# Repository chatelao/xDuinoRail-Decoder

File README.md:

View this project on [CADLAB.io](https://cadlab.io/project/27556). 

# xDuinoRail-Decoder

The friendly decoder development plattform for model railroad tinkers.

## Target plattforms

### Arduino (UNO R3) formfactor

The primary tinker formfactor is the "Arduino UNO R3":

| CPU | MCU | Vendor | Product Name & Page |
|--- | --- | --- | --- | 
| ? Atmega ? | Atmega328 | Arduino & Clones|
|--- | Atmega32u4 | Arduino & Clones |
|--- | AtmegaMEGA | Arduino & Clones |
| ARM M0+ | SAMD21 | Adafruit | [Metro M0 Express](https://www.adafruit.com/product/3505) | 
| ARM M0+ | SAMD21 | SparkFun |
| ARM M4 | SAMD51 | Adafruit | [Metro M4 Express](https://www.adafruit.com/product/4000) | 
| Dual ARM M0+ | RP2040 | Adafruit | [Metro RP2040](https://www.adafruit.com/product/5786) | 
| ARM M4 | nRF52840 | Nordic | [nRF52840 DK](https://www.mouser.ch/ProductDetail/Nordic-Semiconductor/nRF52840-DK?qs=F5EMLAvA7IA76ZLjlwrwMw%3D%3D&gad_source=1&gclid=CjwKCAiA1fqrBhA1EiwAMU5m_9iVmasRrajTl6bT0wZal1_tMu6lTCWF3Ct0FWfQw9FYF_E3vaRdBRoC_tcQAvD_BwE)
| ARM M4 | nRF52840 | Waveshare | [nRF52840 Bluetooth 5.0 Evaluation Kit](https://www.waveshare.com/nrf52840-eval-kit.htm)
| RV32IMAC | SiFive RISC-V | SparkFun | [SparkFun RED-V RedBoard](https://www.sparkfun.com/products/15594) 
| RV32IMAFC | WCH RISC-V | AliExpress | [CH32V307V-EVT-R1 CH32V307 Evaluation Board RISC-V](https://de.aliexpress.com/item/1005004151524708.html)

### Decoder development for XIAO formfactor

The [XIAO](http://www.ulisp.com/show?3NRF) formfactor may even fit some H0 locomotives, so COMING SOON:

| CPU | MCU | Vendor | Product Name & Page |
|--- | --- | --- | --- | 
| ARM M0+ | SAMD21 | SeeedStudio | [XIAO SAMD21](https://wiki.seeedstudio.com/Seeeduino-XIAO)
| Dual ARM M0+ | RP2040 | SeeedStudio | [XIAO RP2040](https://wiki.seeedstudio.com/XIAO-RP2040/)
| ARM M4 | nRF52840  | SeeedStudio | [XIAO BLE](https://wiki.seeedstudio.com/XIAO_BLE/)
| Xtensa LX7  | ESP32-S3 | SeeedStudio | [ESP32-S3](https://wiki.seeedstudio.com/xiao_esp32s3_getting_started/)
| RV32IMC  | ESP32-C3 | SeeedStudio | [ESP32-C3](https://wiki.seeedstudio.com/XIAO_ESP32C3_Getting_Started/) 
| ARM M0+ | SAMD21 | Adafruit | [QT Py SAMD21](https://www.adafruit.com/product/4600) 
| Dual ARM M0+ | RP2040 | Adafruit | [QT Py RP2040](https://www.adafruit.com/product/4900) 
| RV32IMC | ESP32-C3 | Adafruit | [QT Py ESP32-C3](https://www.adafruit.com/product/5405)
| Xtensa LX7 |  ESP32-S2 |Adafruit | [QT Py ESP32-S2](https://www.adafruit.com/product/5325)
| Xtensa LX7  | ESP32-S3 | Adafruit | [QT Py ESP32-S3](https://www.adafruit.com/product/5426)

## Features
Power:
- It extracts power from the rails.

Data
- It extracts DCC raw signals  from the rails.
- It provides raw (RailCom) feedback to the rails.

The data pins are X (input) and Y (output) per default (no soldering needed, but can be reassigned to any other GPIO-Pins.

## Excluded by purpose
- It doesn't include any power IO
- It doesn't include any MCU

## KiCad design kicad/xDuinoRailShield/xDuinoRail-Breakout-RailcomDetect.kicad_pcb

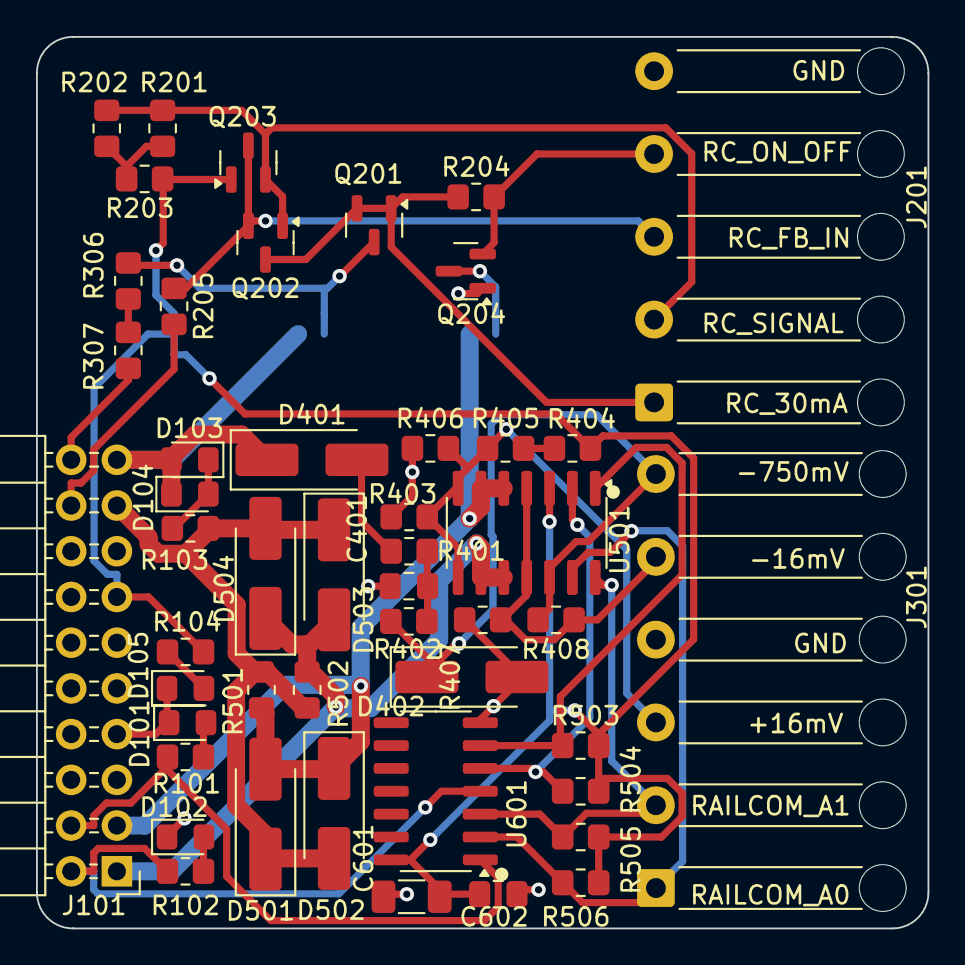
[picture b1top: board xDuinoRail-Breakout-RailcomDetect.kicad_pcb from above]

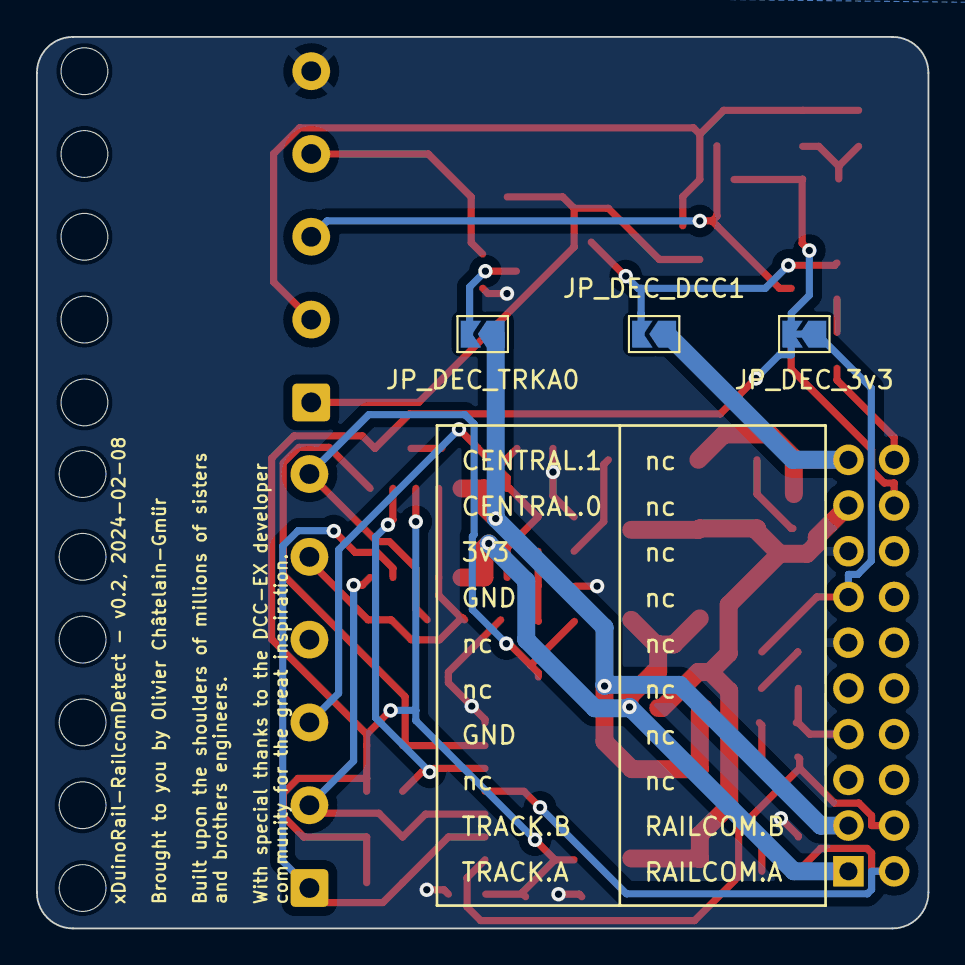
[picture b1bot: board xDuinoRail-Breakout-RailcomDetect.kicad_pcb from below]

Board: 2 copper layers, 49.5 x 49.5 mm, 51 parts (3 on the bottom side), 32 nets.

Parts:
C401: 47uF; C_0805_2012Metric_Pad1.18x1.45mm_HandSolder
C601: 100uF; C_1206_3216Metric_Pad1.33x1.80mm_HandSolder
C602: 100nF; C_0805_2012Metric_Pad1.18x1.45mm_HandSolder
D101: LED_BLUE; LED_0805_2012Metric_Pad1.15x1.40mm_HandSolder
D102: LED_GREEN; LED_0805_2012Metric_Pad1.15x1.40mm_HandSolder
D103: LED_YELLOW; LED_0805_2012Metric_Pad1.15x1.40mm_HandSolder
D104: LED_WHITE; LED_0805_2012Metric_Pad1.15x1.40mm_HandSolder
D105: LED_RED; LED_0805_2012Metric_Pad1.15x1.40mm_HandSolder
D401, D402: SM4007; D_SMA_Handsoldering
D501, D502, D503, D504: SS54; D_SMA_Handsoldering
J101: Conn_02x10_Odd_Even; PinHeader_2x10_P2.54mm_Horizontal
J201: Conn_01x05; SolderWire-0.5sqmm_1x05_P4.6mm_D0.9mm_OD2.1mm_Relief
J301: Conn_01x06; SolderWire-0.5sqmm_1x06_P4.6mm_D0.9mm_OD2.1mm_Relief
JP_DEC_3v3: SolderJumper_2_Open; SolderJumper-2_P1.3mm_Open_TrianglePad1.0x1.5mm
JP_DEC_DCC1: SolderJumper_2_Open; SolderJumper-2_P1.3mm_Open_TrianglePad1.0x1.5mm
JP_DEC_TRKA0: SolderJumper_2_Open; SolderJumper-2_P1.3mm_Open_TrianglePad1.0x1.5mm
Q201, Q204: S8050; SOT-23
Q202, Q203: S8550; SOT-23
R101, R102, R103, R104, R204, R205, R306, R307, R404, R405, R408, R503, R504, R505, R506: 10k; R_0805_2012Metric_Pad1.20x1.40mm_HandSolder
R201, R202, R203: 10R; R_0805_2012Metric_Pad1.20x1.40mm_HandSolder
R401, R402, R403, R406, R407: 220R; R_0805_2012Metric_Pad1.20x1.40mm_HandSolder
R501, R502: 2R; R_0805_2012Metric_Pad1.20x1.40mm_HandSolder
U501: LM339; SOIC-14_3.9x8.7mm_P1.27mm
U601: 74HC02; SOIC-14_3.9x8.7mm_P1.27mm

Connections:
+3V3: C601.1, C602.1, J101.13, JP_DEC_3v3.1 (A), JP_DEC_3v3.2 (B), Q203.1 (E), R104.1, R203.2, R404.2, R503.2, R504.2, R505.2, R506.2, U501.3 (V+), U601.14 (VCC)
+18mV: J301.3, R403.2, R405.1, R406.2, U501.7 (+), U501.8 (-)
-18mV: J301.5, R407.1, R408.1, U501.4 (-), U501.11 (+)
-750mV: D402.1 (K), J301.6, R402.1, R408.2, U501.12 (V-)
/CN_A2: J301.1, R506.1, U501.13, U601.2
/CN_A3: J301.2, R505.1, U501.14, U601.3
/CN_A4: R504.1, U501.2, U601.5
/CN_A5: R503.1, U501.1, U601.6
/DCC0: D501.1 (K), D502.2 (A), D503.1 (K), D504.2 (A), J101.17, R103.1, R501.2, R502.2
/DCC1: D103.2 (A), D104.1 (K), D401.1 (K), J101.19, JP_DEC_DCC1.1 (A)
/DECODER_DIGITAL: J101.20, R307.2
/DECODER_RAILCOM: J101.18, R205.2
/RAILCOM0: J101.4, R101.1, U601.1
/RAILCOM1: J101.2, R102.1, U601.4
/RC_GENERATOR0: JP_DEC_TRKA0.2 (B), Q204.3 (C)
/RC_GENERATOR1: JP_DEC_DCC1.2 (B), Q201.3 (C), R306.1
/TRACK_A0: D501.2 (A), D502.1 (K), J101.3, JP_DEC_TRKA0.1 (A), R501.1, U501.5 (+), U501.6 (-)
/TRACK_B0: D503.2 (A), D504.1 (K), J101.1, R502.1, U501.9 (+), U501.10 (-)
/centrale-railcom-feedback/central_railcom-power-source/DCC_NEG: C401.2, R401.1, R402.2
/rails_signal_feedback_dcc-railcom-8x50/15R: R201.2, R202.2, R203.1
/rails_signal_feedback_dcc-railcom-8x50/RC_CURR: J201.2, Q202.1 (E), Q203.2 (B), R201.1, R202.1
/rails_signal_feedback_dcc-railcom-8x50/RC_FB_IN: J201.3, Q202.2 (B), Q203.3 (C), R205.1
/rails_signal_feedback_dcc-railcom-8x50/RC_ON_OFF: J201.4, Q204.2 (B), R204.2
/rails_signal_feedback_dcc-railcom-8x50/RC_SIGNAL: J201.1, Q201.1 (E), Q201.2 (B), Q202.3 (C), R204.1
GND: C401.1, C601.2, C602.2, D101.1 (K), D102.1 (K), D105.1 (K), D402.2 (A), J101.7, J101.11, J101.15, J201.5, J301.4, Q204.1 (E), R403.1, R406.1, R407.2, U601.7 (GND)
unnamed: D101.2 (A), R101.2
unnamed: D102.2 (A), R102.2
unnamed: D103.1 (K), D104.2 (A), R103.2
unnamed: D105.2 (A), R104.2
unnamed: D401.2 (A), R401.2
unnamed: R306.2, R307.1
unnamed: R404.1, R405.2

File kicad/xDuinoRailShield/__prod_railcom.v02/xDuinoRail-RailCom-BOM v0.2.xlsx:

Reference | Value | Footprint | Qty | LCSC
C401 | 47uF | Capacitor_SMD:C_0805_2012Metric_Pad1.18x1.45mm_HandSolder | 1.0 | C16780
C601 | 100uF | Capacitor_SMD:C_1206_3216Metric_Pad1.33x1.80mm_HandSolder | 1.0 | C15008
C602 | 100nF | Capacitor_SMD:C_0805_2012Metric_Pad1.18x1.45mm_HandSolder | 1.0 | C49678
D101,D102 | LED_GREEN | LED_SMD:LED_0805_2012Metric_Pad1.15x1.40mm_HandSolder | 2.0 | C2297
D103 | LED_YELLOW | LED_SMD:LED_0805_2012Metric_Pad1.15x1.40mm_HandSolder | 1.0 | C2296
D104 | LED_WHITE | LED_SMD:LED_0805_2012Metric_Pad1.15x1.40mm_HandSolder | 1.0 | C34499
D105 | LED_RED | LED_SMD:LED_0805_2012Metric_Pad1.15x1.40mm_HandSolder | 1.0 | C84256
D401,D402 | SM4007 | Diode_SMD:D_SMA_Handsoldering | 2.0 | C64898
D501,D502,D503,D504 | SS54 | Diode_SMD:D_SMA_Handsoldering | 4.0 | C22452
Q201,Q204 | S8050 | Package_TO_SOT_SMD:SOT-23 | 2.0 | C2150
Q202,Q203 | S8550 | Package_TO_SOT_SMD:SOT-23 | 2.0 | C8542
R101,R102,R103,R104,R204,R205,R306,R307,R404,R405,R408,R503,R504,R505,R506 | 10k | Resistor_SMD:R_0805_2012Metric_Pad1.20x1.40mm_HandSolder | 15.0 | C17414
R201,R202,R203 | 10R | Resistor_SMD:R_0805_2012Metric_Pad1.20x1.40mm_HandSolder | 3.0 | C17415
R401,R402,R403,R406,R407 | 220R | Resistor_SMD:R_0805_2012Metric_Pad1.20x1.40mm_HandSolder | 5.0 | C17557
R501,R502 | 2R | Resistor_SMD:R_0805_2012Metric_Pad1.20x1.40mm_HandSolder | 2.0 | C22977
U501 | LM339 | Package_SO:SOIC-14_3.9x8.7mm_P1.27mm | 1.0 | C7948
U601 | 74HC02 | Package_SO:SOIC-14_3.9x8.7mm_P1.27mm | 1.0 | C5588

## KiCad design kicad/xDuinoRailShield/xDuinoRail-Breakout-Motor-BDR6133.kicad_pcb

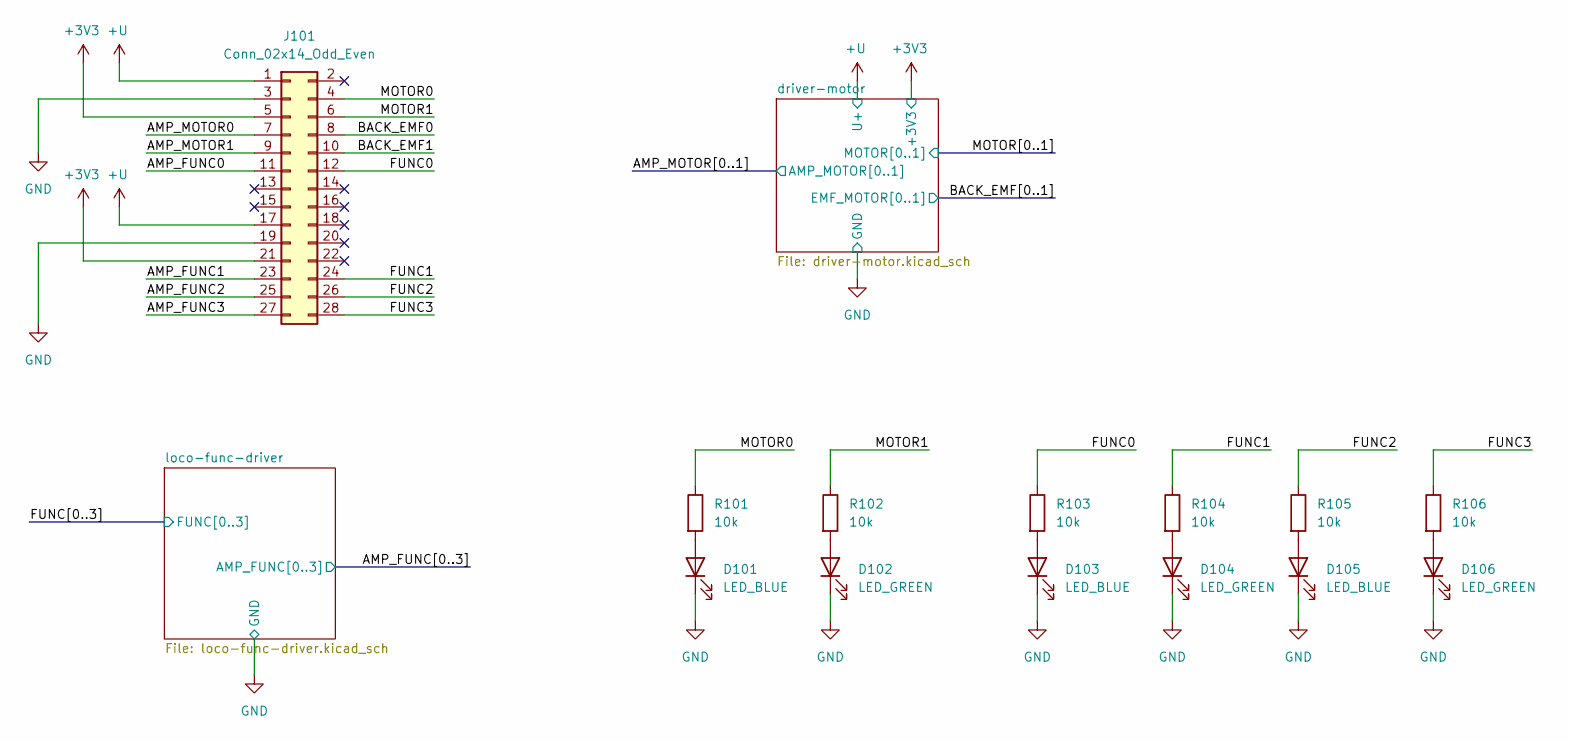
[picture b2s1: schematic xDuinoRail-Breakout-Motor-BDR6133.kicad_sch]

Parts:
D101, D103, D105: LED_BLUE; LED_0805_2012Metric_Pad1.15x1.40mm_HandSolder
D102, D104, D106: LED_GREEN; LED_0805_2012Metric_Pad1.15x1.40mm_HandSolder
J101: Conn_02x14_Odd_Even; PinSocket_2x14_P2.54mm_Horizontal
R101, R102, R103, R104, R105, R106: 10k; R_0805_2012Metric_Pad1.20x1.40mm_HandSolder

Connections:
+3V3: J101.5, J101.21; also elsewhere on the board
+U: J101.1, J101.17; also elsewhere on the board
/AMP_FUNC0: J101.11; also elsewhere on the board
/AMP_FUNC1: J101.23; also elsewhere on the board
/AMP_FUNC2: J101.25; also elsewhere on the board
/AMP_FUNC3: J101.27; also elsewhere on the board
/AMP_MOTOR0: J101.7; also elsewhere on the board
/AMP_MOTOR1: J101.9; also elsewhere on the board
/BACK_EMF0: J101.8; also elsewhere on the board
/BACK_EMF1: J101.10; also elsewhere on the board
/FUNC0: J101.12, R103.1; also elsewhere on the board
/FUNC1: J101.24, R104.1; also elsewhere on the board
/FUNC2: J101.26, R105.1; also elsewhere on the board
/FUNC3: J101.28, R106.1; also elsewhere on the board
/MOTOR0: J101.4, R101.1; also elsewhere on the board
/MOTOR1: J101.6, R102.1; also elsewhere on the board
GND: D101.1 (K), D102.1 (K), D103.1 (K), D104.1 (K), D105.1 (K), D106.1 (K), J101.3, J101.19; also elsewhere on the board
unnamed: D101.2 (A), R101.2
unnamed: D102.2 (A), R102.2
unnamed: D103.2 (A), R103.2
unnamed: D104.2 (A), R104.2
unnamed: D105.2 (A), R105.2
unnamed: D106.2 (A), R106.2

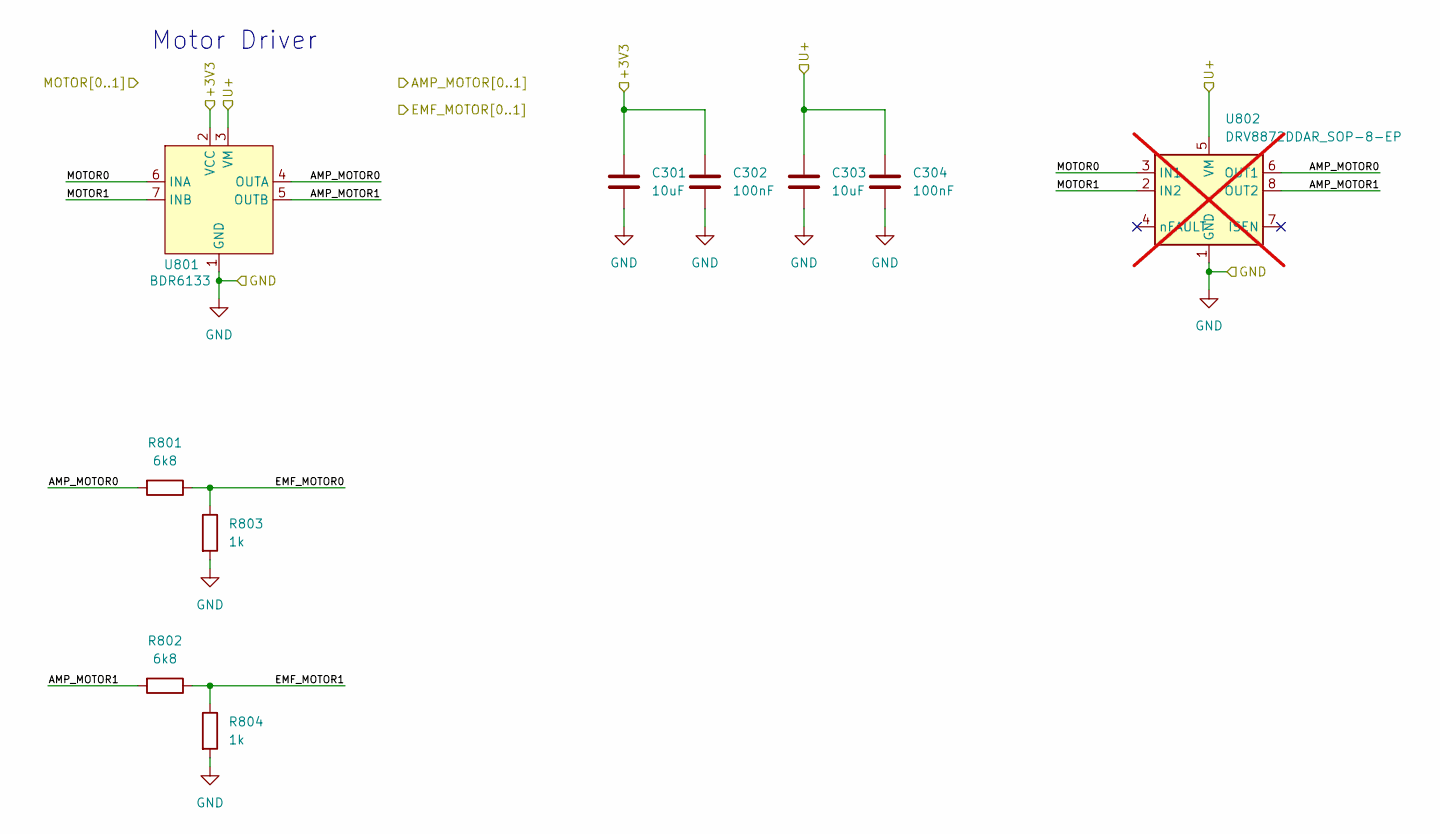
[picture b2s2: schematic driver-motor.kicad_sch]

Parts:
C301, C303: 10uF; C_0805_2012Metric_Pad1.18x1.45mm_HandSolder
C302, C304: 100nF; C_0805_2012Metric_Pad1.18x1.45mm_HandSolder
R801, R802: 6k8; R_0805_2012Metric_Pad1.20x1.40mm_HandSolder
R803, R804: 1k; R_0805_2012Metric_Pad1.20x1.40mm_HandSolder
U801: BDR6133
U802: DRV8872DDAR_SOP-8-EP; Texas_HTSOP-8-1EP_3.9x4.9mm_P1.27mm_EP2.95x4.9mm_Mask2.4x3.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; not fitted

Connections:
+3V3: C301.1, C302.1, U801.2 (VCC); also elsewhere on the board
+U: C303.1, C304.1, U801.3 (VM), U802.5 (VM); also elsewhere on the board
/AMP_MOTOR0: R801.2, U801.4 (OUTA), U802.6 (OUT1); also elsewhere on the board
/AMP_MOTOR1: R802.2, U801.5 (OUTB), U802.8 (OUT2); also elsewhere on the board
/BACK_EMF0: R801.1, R803.1; also elsewhere on the board
/BACK_EMF1: R802.1, R804.1; also elsewhere on the board
/MOTOR0: U801.6 (INA), U802.3 (IN1); also elsewhere on the board
/MOTOR1: U801.7 (INB), U802.2 (IN2); also elsewhere on the board
GND: C301.2, C302.2, C303.2, C304.2, R803.2, R804.2, U801.1 (GND), U802.1 (GND), U802.9 (GND); also elsewhere on the board

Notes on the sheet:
Motor Driver

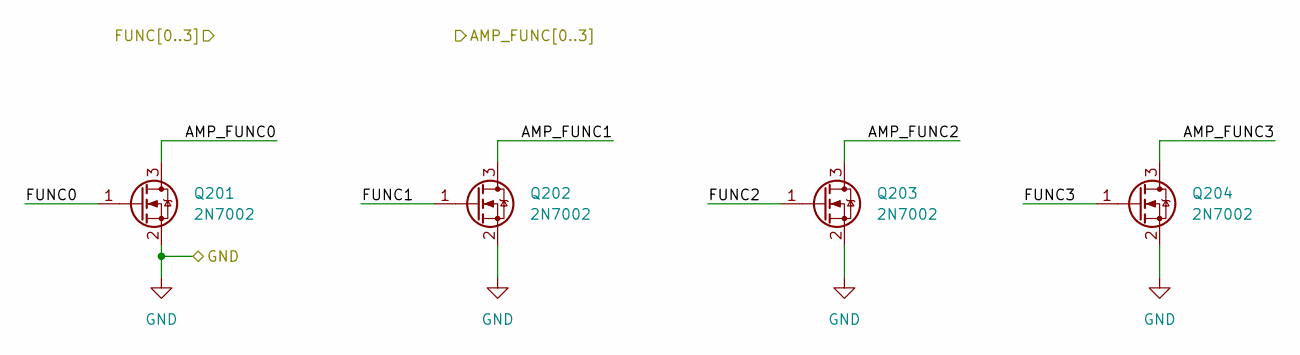
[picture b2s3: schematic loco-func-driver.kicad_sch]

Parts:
Q201, Q202, Q203, Q204: 2N7002; SOT-23

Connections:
/AMP_FUNC0: Q201.3 (D); also elsewhere on the board
/AMP_FUNC1: Q202.3 (D); also elsewhere on the board
/AMP_FUNC2: Q203.3 (D); also elsewhere on the board
/AMP_FUNC3: Q204.3 (D); also elsewhere on the board
/FUNC0: Q201.1 (G); also elsewhere on the board
/FUNC1: Q202.1 (G); also elsewhere on the board
/FUNC2: Q203.1 (G); also elsewhere on the board
/FUNC3: Q204.1 (G); also elsewhere on the board
GND: Q201.2 (S), Q202.2 (S), Q203.2 (S), Q204.2 (S); also elsewhere on the board

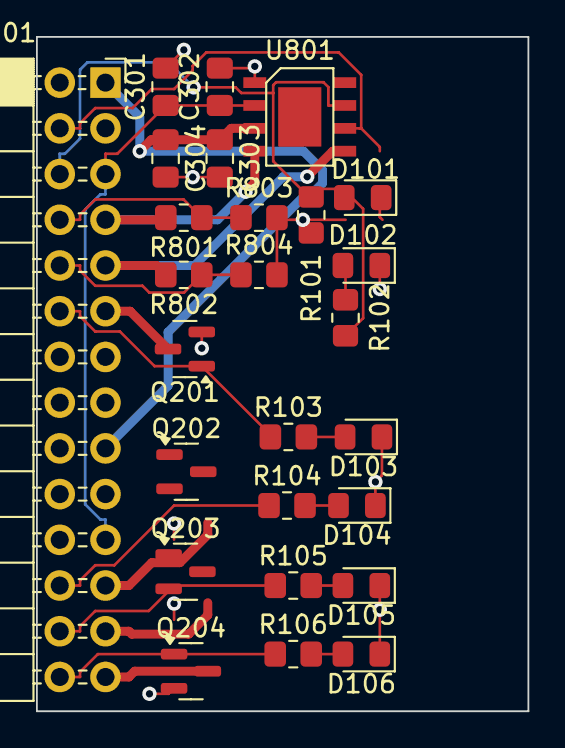
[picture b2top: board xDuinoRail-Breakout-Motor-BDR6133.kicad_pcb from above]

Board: 2 copper layers, 27.3 x 37.5 mm, 26 parts (0 on the bottom side), 23 nets.

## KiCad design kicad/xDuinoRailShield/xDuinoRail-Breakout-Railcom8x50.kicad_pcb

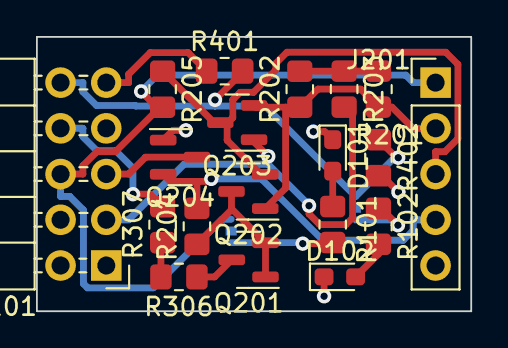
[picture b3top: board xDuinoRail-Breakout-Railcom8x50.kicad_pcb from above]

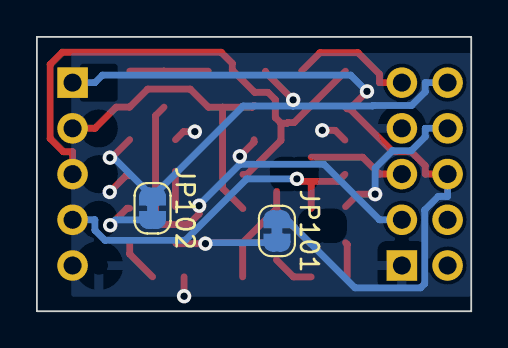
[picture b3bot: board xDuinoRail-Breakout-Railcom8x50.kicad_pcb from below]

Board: 2 copper layers, 24.1 x 15.2 mm, 21 parts (2 on the bottom side), 18 nets.

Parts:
D101, D102: LED; LED_0603_1608Metric_Pad1.05x0.95mm_HandSolder
J101: Conn_02x05_Odd_Even; PinHeader_2x05_P2.54mm_Horizontal
J201: Conn_01x05; PinHeader_1x05_P2.54mm_Vertical
JP101, JP102: SolderJumper_2_Bridged; SolderJumper-2_P1.3mm_Bridged_RoundedPad1.0x1.5mm
Q201, Q204: S8050; SOT-23
Q202, Q203: S8550; SOT-23
R101, R102: 100R; R_0805_2012Metric_Pad1.20x1.40mm_HandSolder
R201, R202, R203: 10R; R_0805_2012Metric_Pad1.20x1.40mm_HandSolder
R204, R205, R306, R307, R401: 10k; R_0805_2012Metric_Pad1.20x1.40mm_HandSolder
R402: 1k; R_0805_2012Metric_Pad1.20x1.40mm_HandSolder

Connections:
+3v3: J101.3, Q203.1 (E), R203.2
+U: J101.9, R401.1
/ACDC_SIGNAL: J101.10, JP102.1 (A), R401.2, R402.1
/DCC0: J101.5, Q204.3 (C)
/DCC1: Q201.3 (C), R306.1
/DCC_MM_SIGNAL: J101.8, R307.2
/RAILCOM_DATA: J101.6, J201.1, JP101.1 (A), R205.2
/rails_signal_feedback_dcc-railcom-8x50/15R: R201.2, R202.2, R203.1
/rails_signal_feedback_dcc-railcom-8x50/RC_CURR: J201.2, Q202.1 (E), Q203.2 (B), R201.1, R202.1
/rails_signal_feedback_dcc-railcom-8x50/RC_FB_IN: J201.3, Q202.2 (B), Q203.3 (C), R205.1
/rails_signal_feedback_dcc-railcom-8x50/RC_ON_OFF: J201.4, Q204.2 (B), R204.2
/rails_signal_feedback_dcc-railcom-8x50/RC_SIGNAL: Q201.1 (E), Q201.2 (B), Q202.3 (C), R204.1
GND: D101.1 (K), D102.1 (K), J101.1, J101.7, J201.5, Q204.1 (E), R402.2
unnamed: D101.2 (A), R101.2
unnamed: D102.2 (A), R102.2
unnamed: JP101.2 (B), R101.1
unnamed: JP102.2 (B), R102.1
unnamed: R306.2, R307.1

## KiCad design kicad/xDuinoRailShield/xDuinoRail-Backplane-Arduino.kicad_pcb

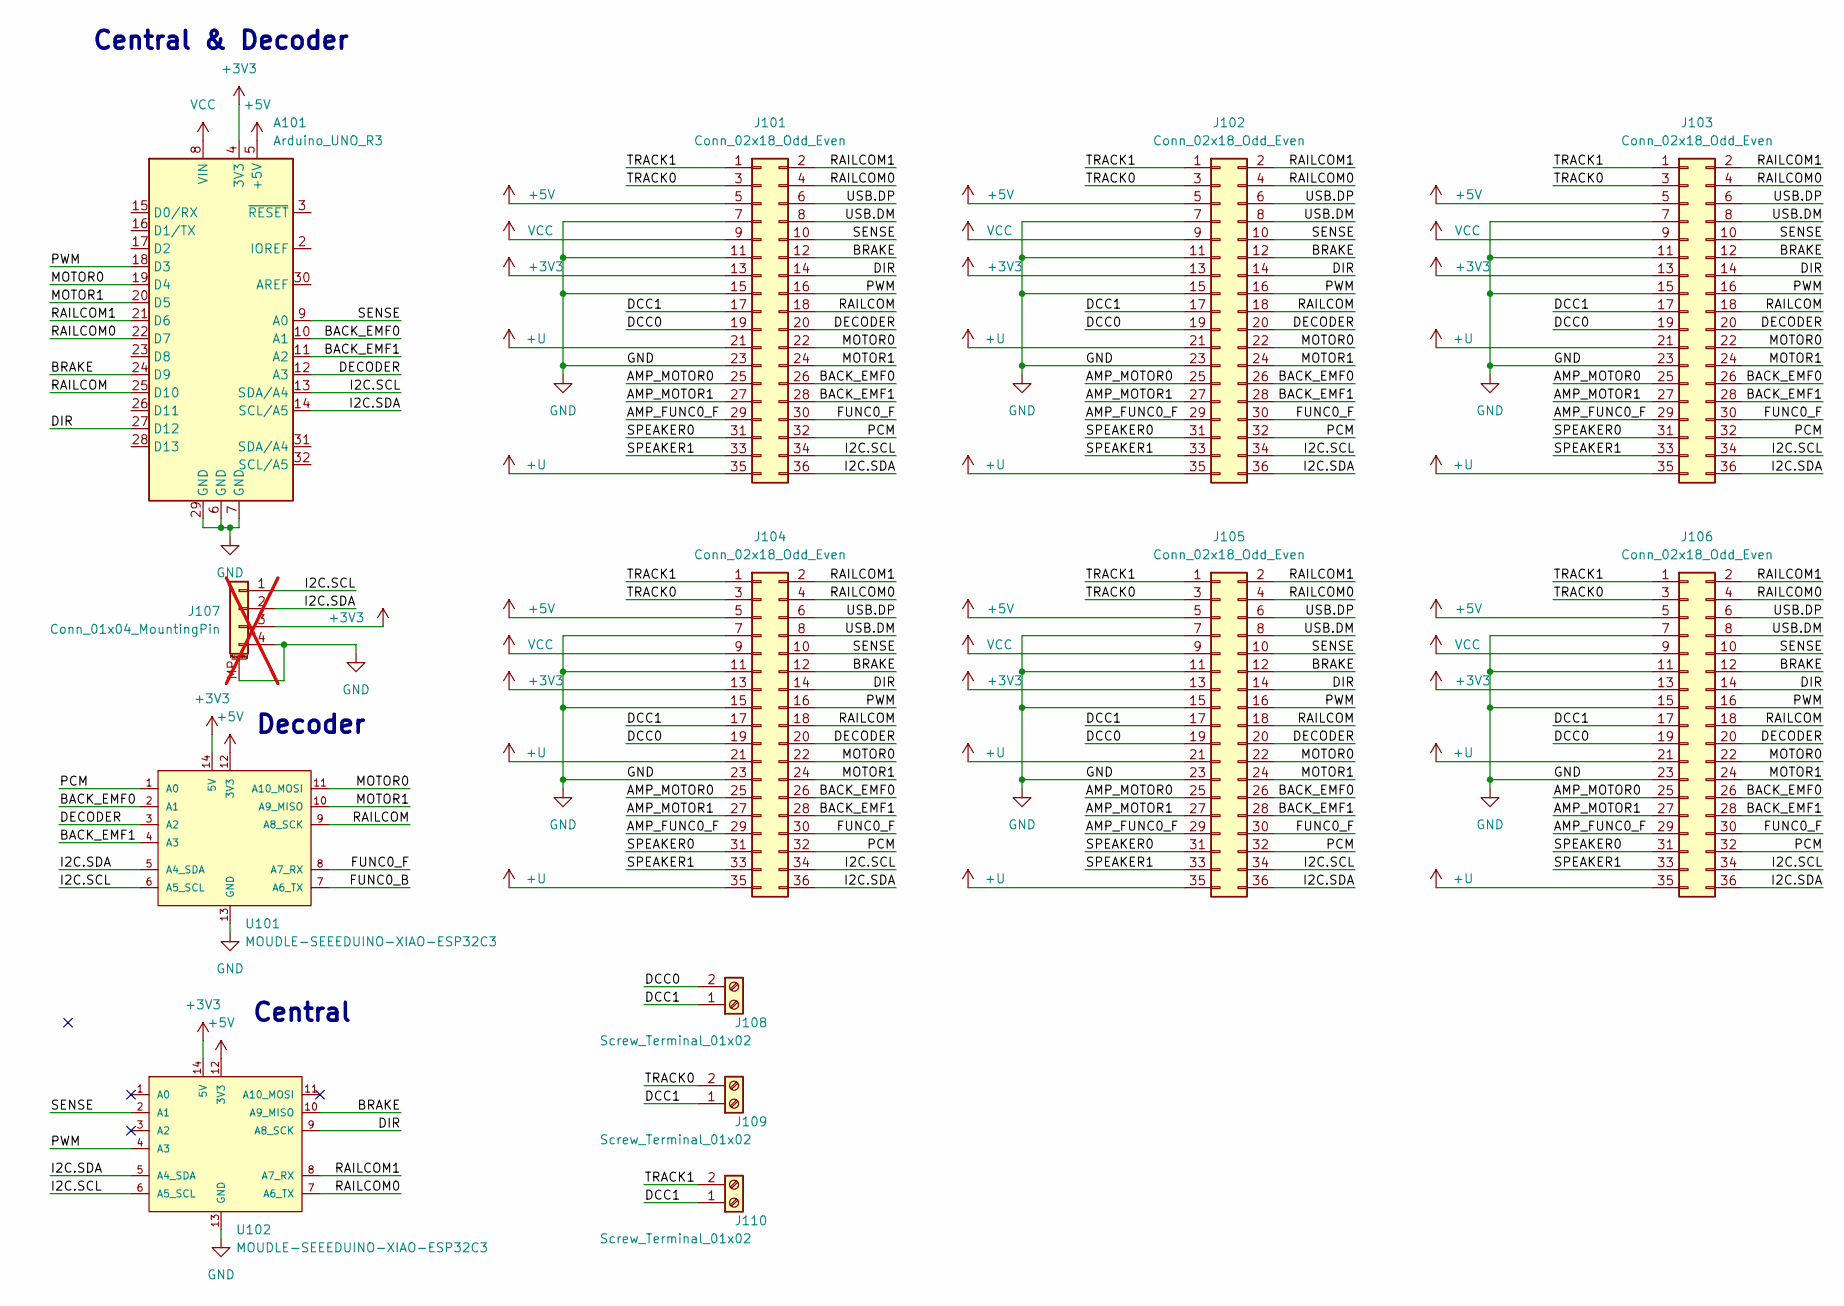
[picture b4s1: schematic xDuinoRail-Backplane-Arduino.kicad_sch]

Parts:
A101: Arduino_UNO_R3
J101, J102, J103, J104, J105, J106: Conn_02x18_Odd_Even; PinSocket_2x18_P2.54mm_Vertical
J107: Conn_01x04_MountingPin; JST_SH_SM04B-SRSS-TB_1x04-1MP_P1.00mm_Horizontal; not fitted
J108, J109, J110: Screw_Terminal_01x02; TerminalBlock_bornier-2_P5.08mm
U101, U102: MOUDLE-SEEEDUINO-XIAO-ESP32C3; MOUDLE14P-SMD-2.54-21X17.8MM

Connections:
+3V3: A101.4 (3V3), J101.13, J102.13, J103.13, J104.13, J105.13, J106.13, J107.3, U101.14 (5V), U102.14 (5V)
+5V: A101.5 (+5V), J101.5, J102.5, J103.5, J104.5, J105.5, J106.5, U101.12 (3V3), U102.12 (3V3)
+U: J101.21, J101.35, J102.21, J102.35, J103.21, J103.35, J104.21, J104.35, J105.21, J105.35, J106.21, J106.35
/AMP_FUNC0_F: J101.29, J102.29, J103.29, J104.29, J105.29, J106.29
/AMP_MOTOR0: J101.25, J102.25, J103.25, J104.25, J105.25, J106.25
/AMP_MOTOR1: J101.27, J102.27, J103.27, J104.27, J105.27, J106.27
/BACK_EMF0: A101.10 (A1), J101.26, J102.26, J103.26, J104.26, J105.26, J106.26, U101.2 (A1)
/BACK_EMF1: A101.11 (A2), J101.28, J102.28, J103.28, J104.28, J105.28, J106.28, U101.4 (A3)
/BRAKE: A101.24 (D9), J101.12, J102.12, J103.12, J104.12, J105.12, J106.12, U102.10 (A9_MISO)
/DCC0: J101.19, J102.19, J103.19, J104.19, J105.19, J106.19, J108.2
/DCC1: J101.17, J102.17, J103.17, J104.17, J105.17, J106.17, J108.1, J109.1, J110.1
/DECODER: A101.12 (A3), J101.20, J102.20, J103.20, J104.20, J105.20, J106.20, U101.3 (A2)
/DIR: A101.27 (D12), J101.14, J102.14, J103.14, J104.14, J105.14, J106.14, U102.9 (A8_SCK)
/FUNC0_B: U101.7 (A6_TX)
/FUNC0_F: J101.30, J102.30, J103.30, J104.30, J105.30, J106.30, U101.8 (A7_RX)
/I2C.SCL: A101.13 (SDA/A4), J101.34, J102.34, J103.34, J104.34, J105.34, J106.34, J107.1, U101.6 (A5_SCL), U102.6 (A5_SCL)
/I2C.SDA: A101.14 (SCL/A5), J101.36, J102.36, J103.36, J104.36, J105.36, J106.36, J107.2, U101.5 (A4_SDA), U102.5 (A4_SDA)
/MOTOR0: A101.19 (D4), J101.22, J102.22, J103.22, J104.22, J105.22, J106.22, U101.11 (A10_MOSI)
/MOTOR1: A101.20 (D5), J101.24, J102.24, J103.24, J104.24, J105.24, J106.24, U101.10 (A9_MISO)
/PCM: J101.32, J102.32, J103.32, J104.32, J105.32, J106.32, U101.1 (A0)
/PWM: A101.18 (D3), J101.16, J102.16, J103.16, J104.16, J105.16, J106.16, U102.4 (A3)
/RAILCOM: A101.25 (D10), J101.18, J102.18, J103.18, J104.18, J105.18, J106.18, U101.9 (A8_SCK)
/RAILCOM0: A101.22 (D7), J101.4, J102.4, J103.4, J104.4, J105.4, J106.4, U102.7 (A6_TX)
/RAILCOM1: A101.21 (D6), J101.2, J102.2, J103.2, J104.2, J105.2, J106.2, U102.8 (A7_RX)
/SENSE: A101.9 (A0), J101.10, J102.10, J103.10, J104.10, J105.10, J106.10, U102.2 (A1)
/SPEAKER0: J101.31, J102.31, J103.31, J104.31, J105.31, J106.31
/SPEAKER1: J101.33, J102.33, J103.33, J104.33, J105.33, J106.33
/TRACK0: J101.3, J102.3, J103.3, J104.3, J105.3, J106.3, J109.2
/TRACK1: J101.1, J102.1, J103.1, J104.1, J105.1, J106.1, J110.2
/USB.DM: J101.8, J102.8, J103.8, J104.8, J105.8, J106.8
/USB.DP: J101.6, J102.6, J103.6, J104.6, J105.6, J106.6
GND: A101.6 (GND), A101.7 (GND), A101.29 (GND), J101.7, J101.11, J101.15, J101.23, J102.7, J102.11, J102.15, J102.23, J103.7, J103.11, J103.15, J103.23, J104.7, J104.11, J104.15, J104.23, J105.7, J105.11, J105.15, J105.23, J106.7, J106.11, J106.15, J106.23, J107.4, J107.MP (MountPin), U101.13 (GND), U102.13 (GND)
VCC: A101.8 (VIN), J101.9, J102.9, J103.9, J104.9, J105.9, J106.9

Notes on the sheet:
Central
Central & Decoder
Decoder

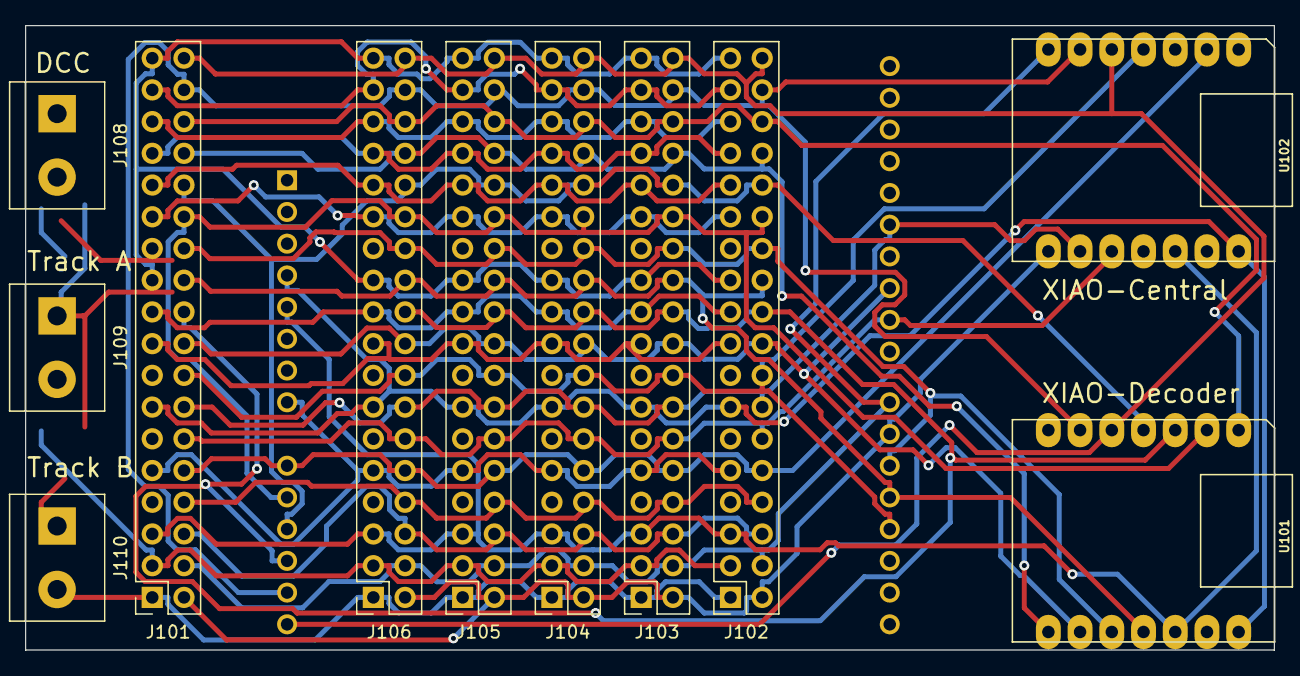
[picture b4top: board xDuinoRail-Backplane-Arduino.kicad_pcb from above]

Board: 2 copper layers, 100.0 x 50.0 mm, 12 parts (1 on the bottom side), 32 nets.
